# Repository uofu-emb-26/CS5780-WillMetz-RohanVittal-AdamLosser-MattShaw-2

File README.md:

# CS5780 Final Project
# Nixie Tube Sound Meter

## Rohan Vittal, Will Metz, Adam Losser, and Matt Shaw 

A nixie tube driver that displays real-time microphone loudness as a percentage (0–100) across four ZM1000 nixie tubes. Audio is sampled via an onboard microphone through the STM32's ADC, processed into a loudness percentage, and transmitted over UART to a PC while simultaneously driving the nixie display.

## System Overview:
The system consists of three physical boards:

- STM32F072 Discovery — microcontroller, ADC microphone input, UART output, GPIO drive
- Custom PCB — contains K155ID1 (К155ИД1) BCD driver ICs, HV power distribution, and connectors
- [HV Power Board](https://ebay.us/m/Hubveg) — MAX1771 boost converter (160–210V output), 5V logic input
See [BOM](./BOM.md) for a detailed list of components.

The STM32 extracts digits from the loudness percentage and writes 4-bit BCD values to GPIO pins. Each set of 4 GPIO pins drives one K155ID1 BCD decoder IC, which selects the corresponding cathode on each ZM1000 tube. The anode of each tube is supplied with ~170V.

## Software: 
[mic_test](./mic_test/) contains the code that runs on the STM32. To flash, connect the STM32 discovery to USB, and use the cmake command

```bash
cmake --build build --target mic_test
```
### Software Structure
| File | Description |
|---|---|
| `main.c` | Main loop — ADC sampling, smoothing, UART transmit, nixie write |
| `nixie_drivers.c` | Digit extraction, BCD remapping, GPIO write |
| `adc_mic.c` | ADC initialisation and peak-to-peak measurement |
| `uart.c` | UART3 initialisation and byte transmit |
| `board.c` | SysTick, delay, LED bar (unused) |
| `stm32f0xx_it.c` | SysTick interrupt handler |

### GPIO Pin mappings: 
| Tube | MSB | — | — | LSB |
|---|---|---|---|---|
| Tube 4 (hundreds) | PC9 | PC8 | PC7 | PC6 |
| Tube 3 (tens) | PA11 | PA10 | PA9 | PA8 |
| Tube 2 (ones) | PB11 | PB10 | PB9 | PB8 |
| Tube 1 (tenths) | PB7 | PB6 | PB5 | PB4 |

### BCD Remapping

Due to physical wiring errors on the PCB, a lookup table in firmware remaps intended digits to the correct GPIO pattern:

```c
static const uint8_t digit_map[10] = {
    0b1101, // 0
    0b0001, // 1
    0b1001, // 2
    0b0000, // 3
    0b1110, // 4
    0b0110, // 5
    0b1010, // 6
    0b0010, // 7
    0b1000, // 8
    0b0100  // 9
};
```

## Hardware Notes

- **HV polarity** — the eBay HV power board has reversed polarity output terminals. Verify with a multimeter before connecting to the PCB.
- **HV and logic ground** — must be tied to a common ground, either through the screw terminal or using a breadboard. Separate grounds will prevent cathode current return and the tube will not display any digit.
- **Primer pin** — the ZM1000 primer pin is left floating. A 10MΩ resistor to the anode is recommended per the datasheet for strobed applications but is not required for basic DC operation.
- **USB power** — the micro-USB connector footprint on the PCB was incorrect. It is more reliable to attach 5V power directly by soldering a wire or header on in lieu of the microUSB. 

[fixedSN74141N](./fixedSN74141N/) is a converted KiCAD footprint for the TI SN74141N IC (Identical to the Soviet К155ИД1). 

[nixie_driver](./nixie_driver/) is the KiCAD project for our custom PCB. It takes a 170VDC and 5VDC input, as well as 16 GPIOs for BCD number input. Note that the high voltage and 5V side need to share a common grounding.

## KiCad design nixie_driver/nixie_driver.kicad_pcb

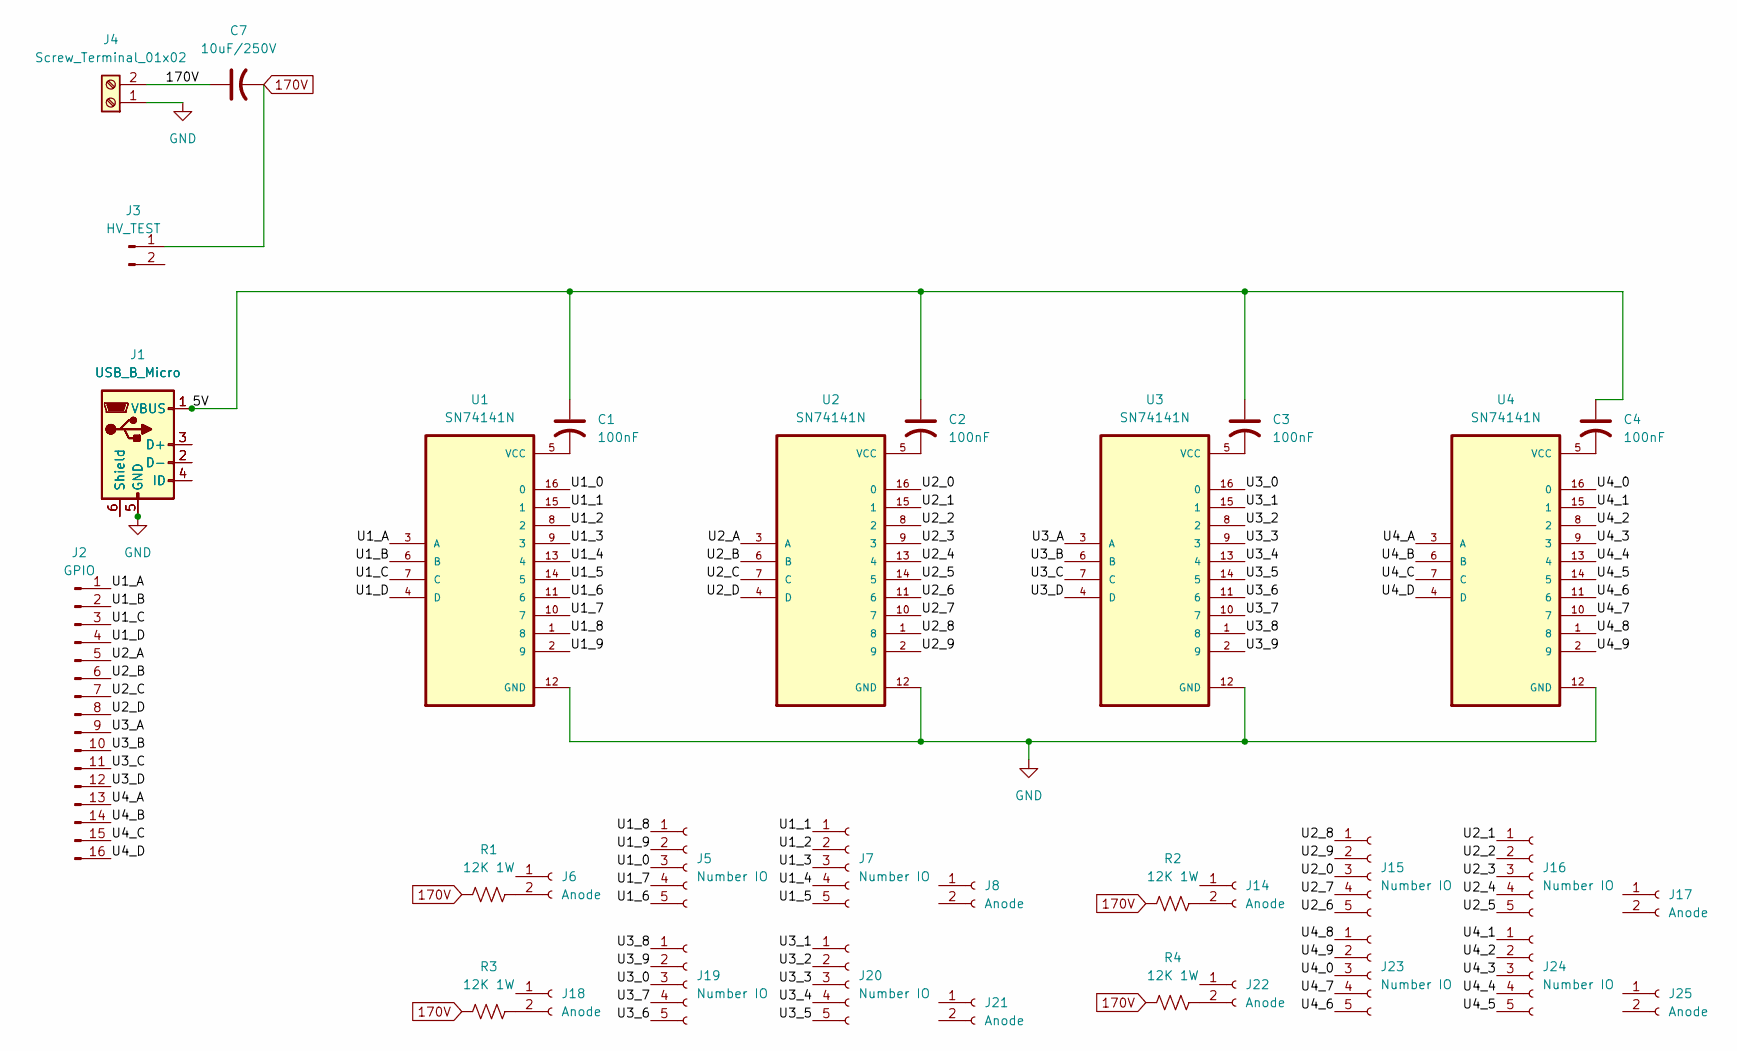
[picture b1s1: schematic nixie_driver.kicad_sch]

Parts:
C1, C2, C3, C4: 100nF; C_0805_2012Metric_Pad1.18x1.45mm_HandSolder
C7: 10uF/250V; CP_Radial_D8.0mm_P3.50mm
J1: USB_B_Micro; USB_Micro-AB_Molex_47590-0001
J2: GPIO; PinHeader_1x16_P2.54mm_Vertical
J3: HV_TEST; PinHeader_1x02_P2.54mm_Vertical
J4: Screw_Terminal_01x02; TerminalBlock_MetzConnect_Type011_RT05502HBLC_1x02_P5.00mm_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
J5, J7, J15, J16, J19, J20, J23, J24: Number IO; PinSocket_1x05_P2.54mm_Vertical
J6, J8, J14, J17, J18, J21, J22, J25: Anode; PinSocket_1x02_P2.54mm_Vertical
J13: USB_B_Micro
R1, R2, R3, R4: 12K 1W; R_Axial_DIN0414_L11.9mm_D4.5mm_P20.32mm_Horizontal
U1, U2, U3, U4: SN74141N; DIP762W46P254L2134H508Q16

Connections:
170V: C7.1, C7.2, J3.1, J4.2, R1.1, R2.1, R3.1, R4.1
/5V: C1.1, C2.1, C3.1, C4.1, J1.1 (VBUS), J13.1 (VBUS)
/U1_0: J5.3, U1.16 (0)
/U1_1: J7.1, U1.15 (1)
/U1_2: J7.2, U1.8 (2)
/U1_3: J7.3, U1.9 (3)
/U1_4: J7.4, U1.13 (4)
/U1_5: J7.5, U1.14 (5)
/U1_6: J5.5, U1.11 (6)
/U1_7: J5.4, U1.10 (7)
/U1_8: J5.1, U1.1 (8)
/U1_9: J5.2, U1.2 (9)
/U1_A: J2.1, U1.3 (A)
/U1_B: J2.2, U1.6 (B)
/U1_C: J2.3, U1.7 (C)
/U1_D: J2.4, U1.4 (D)
/U2_0: J15.3, U2.16 (0)
/U2_1: J16.1, U2.15 (1)
/U2_2: J16.2, U2.8 (2)
/U2_3: J16.3, U2.9 (3)
/U2_4: J16.4, U2.13 (4)
/U2_5: J16.5, U2.14 (5)
/U2_6: J15.5, U2.11 (6)
/U2_7: J15.4, U2.10 (7)
/U2_8: J15.1, U2.1 (8)
/U2_9: J15.2, U2.2 (9)
/U2_A: J2.5, U2.3 (A)
/U2_B: J2.6, U2.6 (B)
/U2_C: J2.7, U2.7 (C)
/U2_D: J2.8, U2.4 (D)
/U3_0: J19.3, U3.16 (0)
/U3_1: J20.1, U3.15 (1)
/U3_2: J20.2, U3.8 (2)
/U3_3: J20.3, U3.9 (3)
/U3_4: J20.4, U3.13 (4)
/U3_5: J20.5, U3.14 (5)
/U3_6: J19.5, U3.11 (6)
/U3_7: J19.4, U3.10 (7)
/U3_8: J19.1, U3.1 (8)
/U3_9: J19.2, U3.2 (9)
/U3_A: J2.9, U3.3 (A)
/U3_B: J2.10, U3.6 (B)
/U3_C: J2.11, U3.7 (C)
/U3_D: J2.12, U3.4 (D)
/U4_0: J23.3, U4.16 (0)
/U4_1: J24.1, U4.15 (1)
/U4_2: J24.2, U4.8 (2)
/U4_3: J24.3, U4.9 (3)
/U4_4: J24.4, U4.13 (4)
/U4_5: J24.5, U4.14 (5)
/U4_6: J23.5, U4.11 (6)
/U4_7: J23.4, U4.10 (7)
/U4_8: J23.1, U4.1 (8)
/U4_9: J23.2, U4.2 (9)
/U4_A: J2.13, U4.3 (A)
/U4_B: J2.14, U4.6 (B)
/U4_C: J2.15, U4.7 (C)
/U4_D: J2.16, U4.4 (D)
GND: J1.5 (GND), J4.1, J13.5 (GND), U1.12 (GND), U2.12 (GND), U3.12 (GND), U4.12 (GND)
unnamed: J1.3 (D+), J13.3 (D+)
unnamed: J1.2 (D-), J13.2 (D-)
unnamed: J1.4 (ID), J13.4 (ID)
unnamed: J1.6 (Shield), J13.6 (Shield)
unnamed: J6.2, R1.2
unnamed: J14.2, R2.2
unnamed: J18.2, R3.2
unnamed: J22.2, R4.2
unnamed: C1.2, U1.5 (VCC)
unnamed: C2.2, U2.5 (VCC)
unnamed: C3.2, U3.5 (VCC)
unnamed: C4.2, U4.5 (VCC)

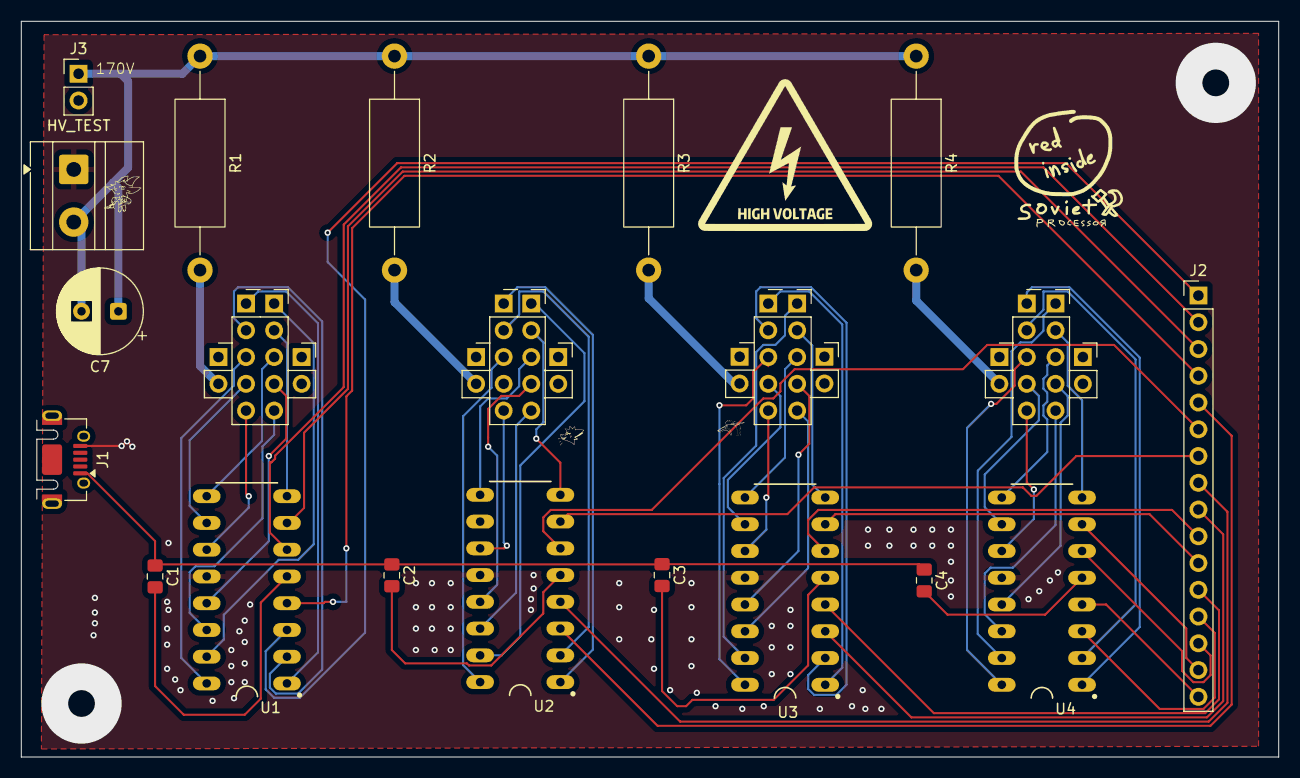
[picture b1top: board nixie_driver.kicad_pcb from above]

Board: 2 copper layers, 119.4 x 69.8 mm, 33 parts (0 on the bottom side), 67 nets.

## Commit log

2026-03-23 README
2026-03-26 added pcb and schema
2026-04-03 mic volume to led code
2026-04-03 mic volume reading
2026-04-03 not just build files this time...
2026-04-08 redoing stuff
2026-04-08 imports
2026-04-08 fixed deisgn
2026-04-09 mostly done
2026-04-09 more label
2026-04-09 schematic done
2026-04-09 gitignire
2026-04-10 new PCB
2026-04-10 polishing of pcb some issues still
2026-04-22 finished nixie driver code and uart code
2026-04-27 add lookup table thing for messed up mappings
2026-04-27 fixed minor bugs in lookup table
2026-04-27 updated pcb
2026-04-27 fixed connection on chip3
2026-04-27 Update .gitignore to include additional patterns
2026-04-27 Revise README with project details and contributors
    Updated project title and added team members and project details.
2026-04-30 update bom
